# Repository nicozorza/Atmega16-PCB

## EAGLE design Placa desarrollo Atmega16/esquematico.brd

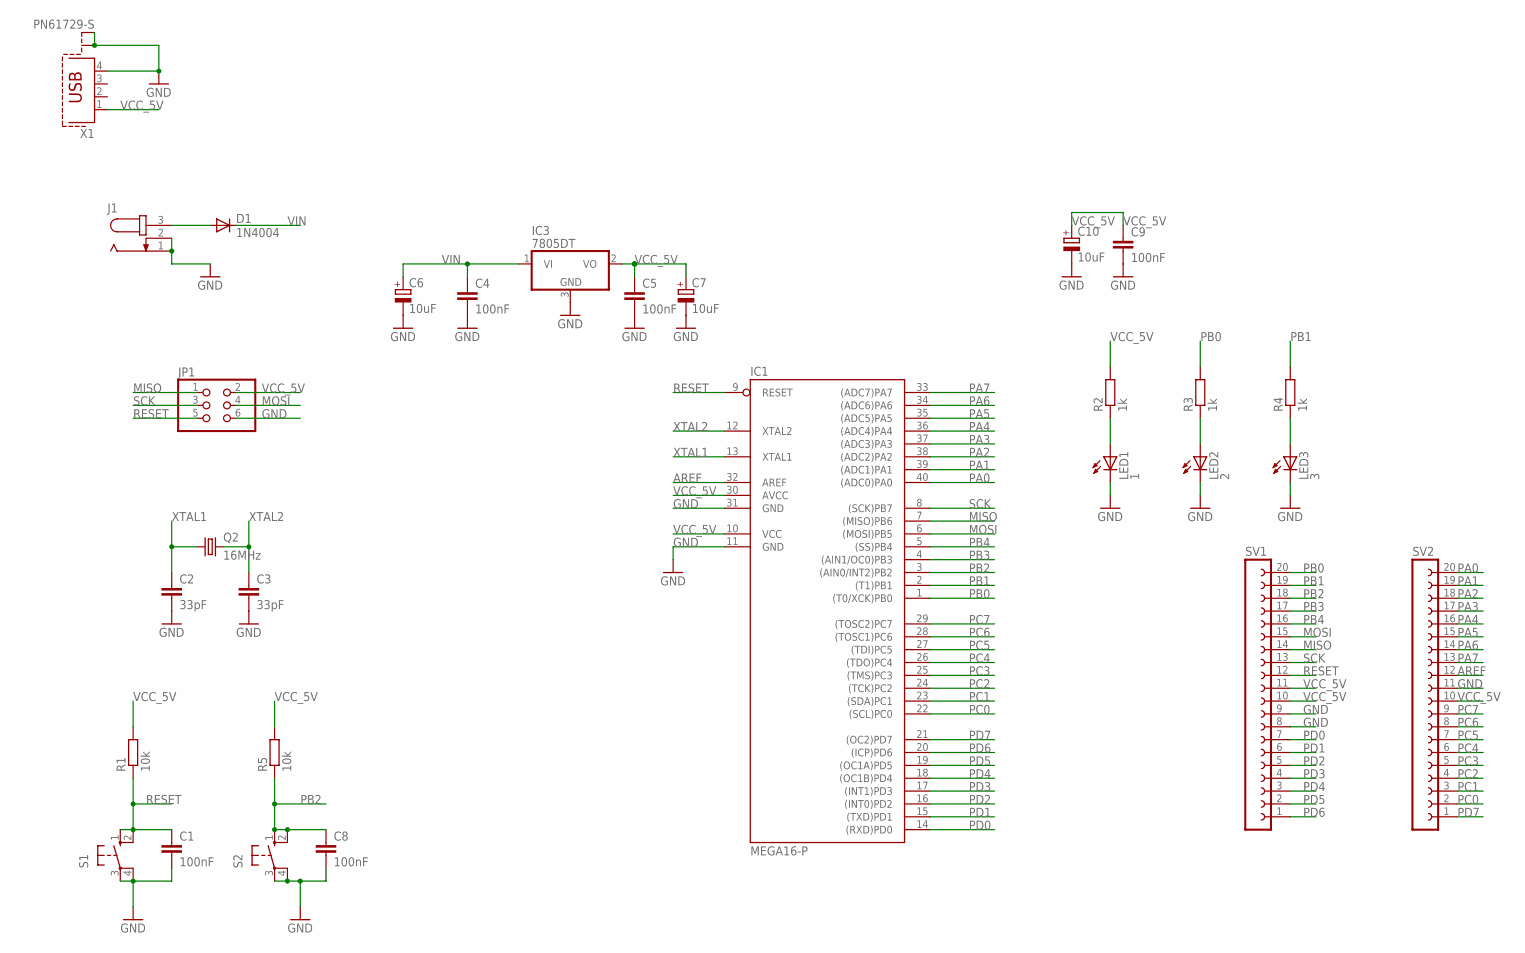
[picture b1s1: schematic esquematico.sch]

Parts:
C1, C4, C5, C8, C9: 100nF; C1206
C2, C3: 33pF; C1206
C6, C7, C10: 10uF; E2,5-6E
D1: 1N4004; DO41-10
IC1: MEGA16-P; DIL40
IC3: 7805DT; TO252
J1: JACK-PLUG1; SPC4078
JP1: PINHD-2X3; 2X03
LED1: 1; LED3MM
LED2: 2; LED3MM
LED3: 3; LED3MM
Q2: 16MHz; HC49/S
R1, R5: 10k; R1206
R2, R3, R4: 1k; R1206
S1, S2: 10-XX; B3F-10XX
SV1, SV2: FE20-1; FE20
X1: PN61729-S

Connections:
AREF: IC1.32 (AREF), SV2.12
GND: C1.2, C2.2, C3.2, C4.2, C5.2, C6.-, C7.-, C8.2, C9.2, C10.-, IC1.11 (GND), IC1.31 (GND), IC3.3 (GND), J1.1, J1.2, JP1.6, LED1.K (C), LED2.K (C), LED3.K (C), S1.3, S1.4 (P1), S2.3, S2.4 (P1), SV1.8, SV1.9, SV2.11, X1.4, X1.S1, X1.S2
MISO: IC1.7 ((MISO)PB6), JP1.1, SV1.14
MOSI: IC1.6 ((MOSI)PB5), JP1.4, SV1.15
unnamed: LED1.A, R2.1
unnamed: LED2.A, R3.1
unnamed: LED3.A, R4.1
unnamed: D1.A, J1.3
PA0: IC1.40 ((ADC0)PA0), SV2.20
PA1: IC1.39 ((ADC1)PA1), SV2.19
PA2: IC1.38 ((ADC2)PA2), SV2.18
PA3: IC1.37 ((ADC3)PA3), SV2.17
PA4: IC1.36 ((ADC4)PA4), SV2.16
PA5: IC1.35 ((ADC5)PA5), SV2.15
PA6: IC1.34 ((ADC6)PA6), SV2.14
PA7: IC1.33 ((ADC7)PA7), SV2.13
PB0: IC1.1 ((T0/XCK)PB0), R3.2, SV1.20
PB1: IC1.2 ((T1)PB1), R4.2, SV1.19
PB2: C8.1, IC1.3 ((AIN0/INT2)PB2), R5.1, S2.1 (S), S2.2 (S1), SV1.18
PB3: IC1.4 ((AIN1/OC0)PB3), SV1.17
PB4: IC1.5 ((SS)PB4), SV1.16
PC0: IC1.22 ((SCL)PC0), SV2.2
PC1: IC1.23 ((SDA)PC1), SV2.3
PC2: IC1.24 ((TCK)PC2), SV2.4
PC3: IC1.25 ((TMS)PC3), SV2.5
PC4: IC1.26 ((TDO)PC4), SV2.6
PC5: IC1.27 ((TDI)PC5), SV2.7
PC6: IC1.28 ((TOSC1)PC6), SV2.8
PC7: IC1.29 ((TOSC2)PC7), SV2.9
PD0: IC1.14 ((RXD)PD0), SV1.7
PD1: IC1.15 ((TXD)PD1), SV1.6
PD2: IC1.16 ((INT0)PD2), SV1.5
PD3: IC1.17 ((INT1)PD3), SV1.4
PD4: IC1.18 ((OC1B)PD4), SV1.3
PD5: IC1.19 ((OC1A)PD5), SV1.2
PD6: IC1.20 ((ICP)PD6), SV1.1
PD7: IC1.21 ((OC2)PD7), SV2.1
RESET: C1.1, IC1.9 (RESET), JP1.5, R1.1, S1.1 (S), S1.2 (S1), SV1.12
SCK: IC1.8 ((SCK)PB7), JP1.3, SV1.13
VCC_5V: C5.1, C7.+, C9.1, C10.+, IC1.10 (VCC), IC1.30 (AVCC), IC3.2 (VO), JP1.2, R1.2, R2.2, R5.2, SV1.10, SV1.11, SV2.10, X1.1
VIN: C4.1, C6.+, D1.C, IC3.1 (VI)
XTAL1: C2.1, IC1.13 (XTAL1), Q2.1
XTAL2: C3.1, IC1.12 (XTAL2), Q2.2

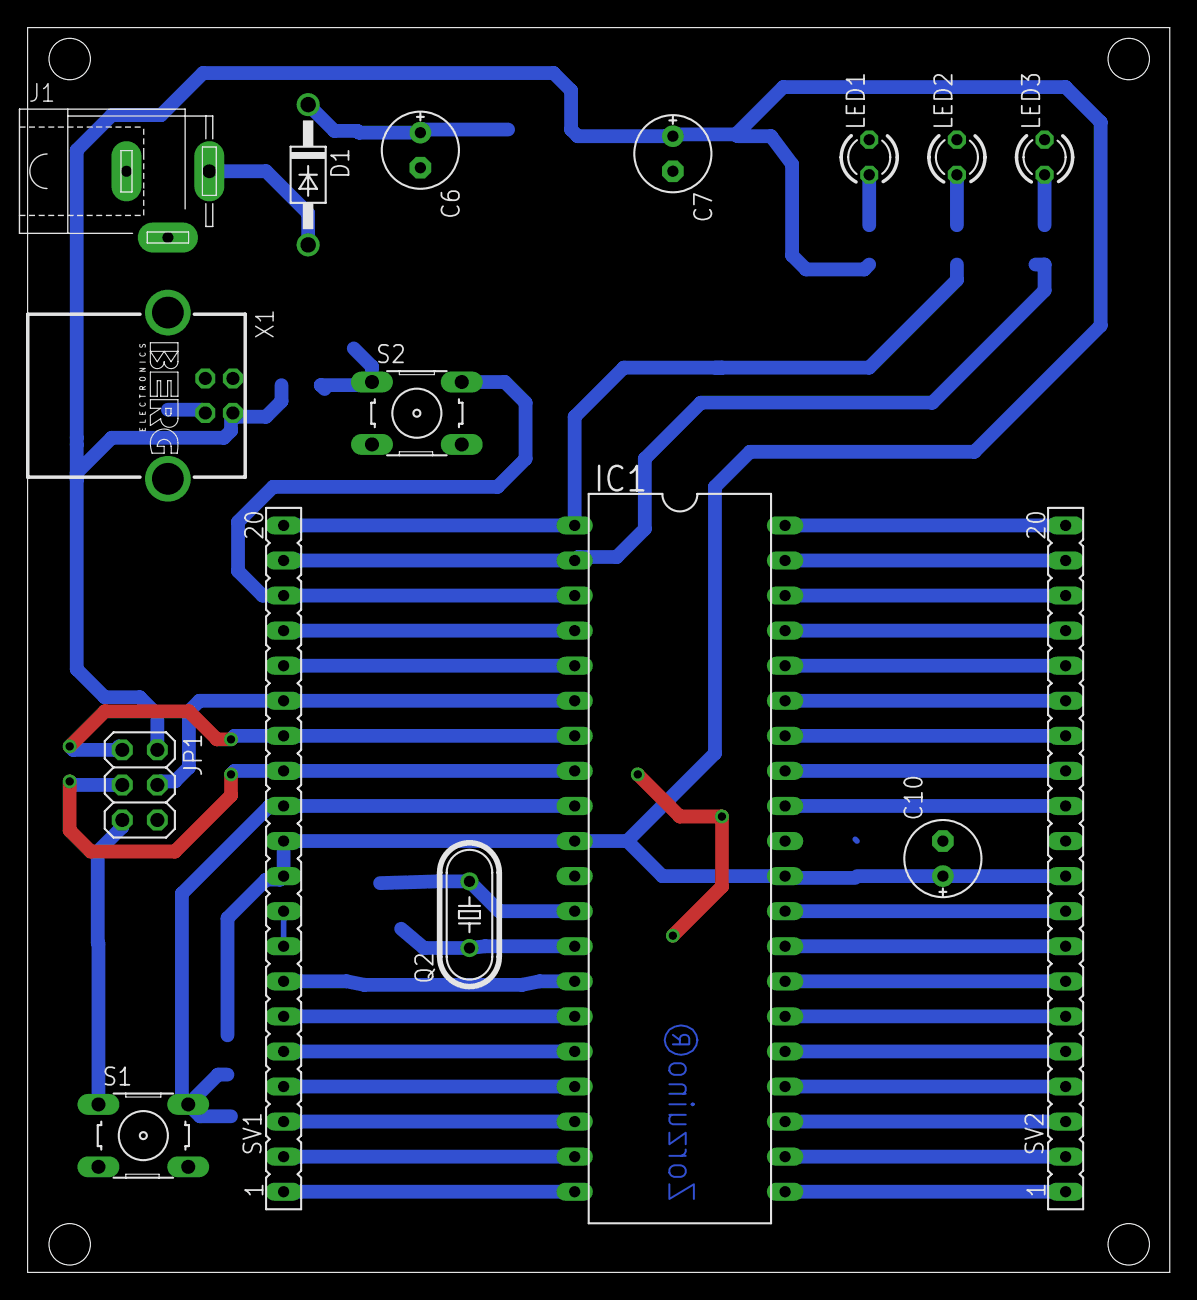
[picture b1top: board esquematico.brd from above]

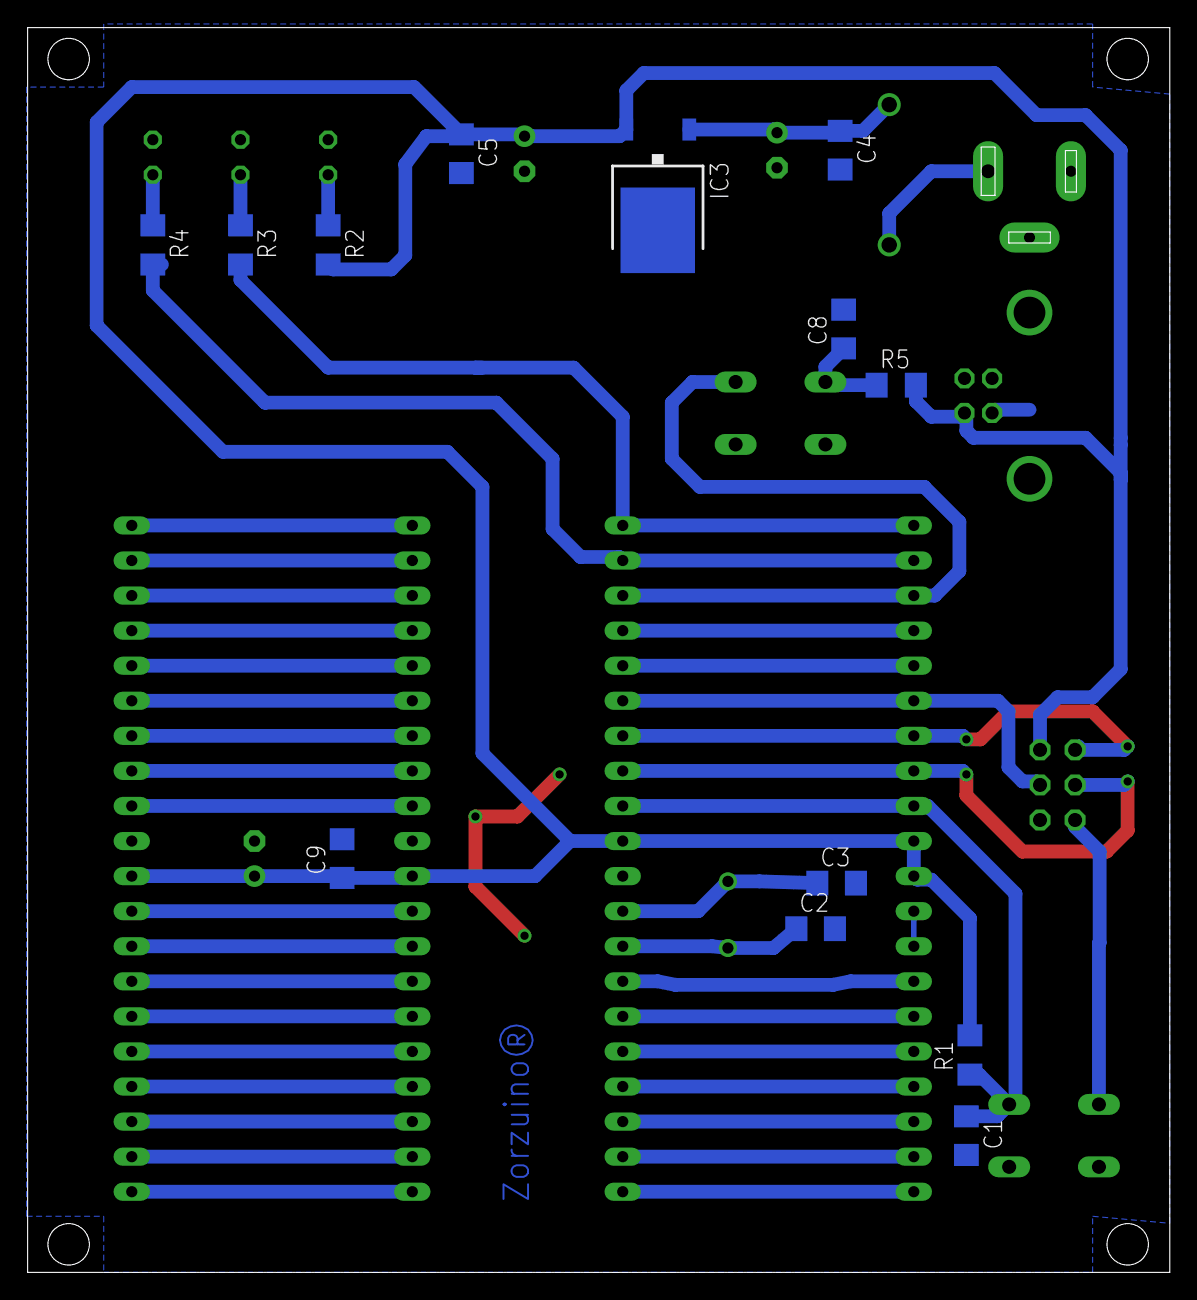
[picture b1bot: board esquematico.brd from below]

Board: 2 copper layers, 82.7 x 90.2 mm, 29 parts (13 on the bottom side), 43 nets.

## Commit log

2017-03-16 PCB sin rutear
2017-03-16 PCB ruteado
2017-03-16 Me faltaba agregar los agujeros para las patitas
2017-03-16 Agregué el nombre de la placa
2017-03-16 Modifique el jumper del lm7833
2017-03-17 Modifique el ancho de las pistas. Hay algunos problemas con la interconexion de masas
2017-03-17 Supuestamente corregi el tema de las masas
2017-03-18 Actualicé el pdf que se necesita para imprimir
2017-03-18 Estoy probando el merge
